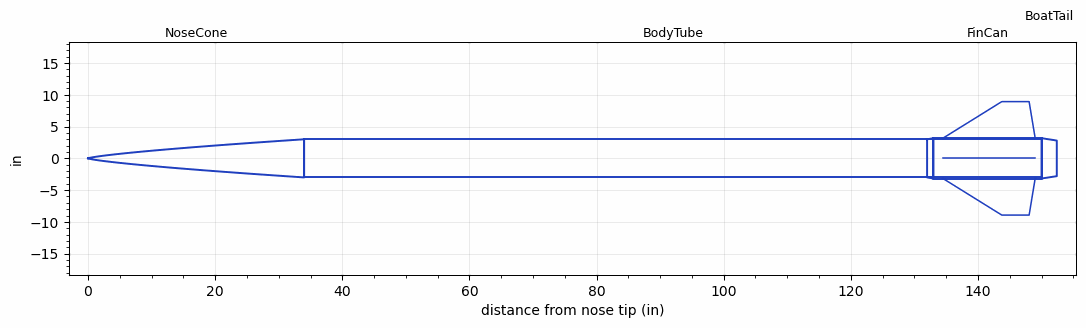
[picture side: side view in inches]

<RASAeroDocument>
 <FileVersion>2</FileVersion>
 <RocketDesign>
  <NoseCone>
   <Length>34</Length>
   <Diameter>6</Diameter>
   <Shape>Power Law</Shape>
   <BluntRadius>0.125</BluntRadius>
   <Location>0</Location>
   <PowerLaw>0.75</PowerLaw>
  </NoseCone>
  <BodyTube>
   <Length>116</Length>
   <Diameter>6</Diameter>
   <Location>34</Location>
  </BodyTube>
  <FinCan>
   <Length>17</Length>
   <Diameter>6.35</Diameter>
   <InsideDiameter>6</InsideDiameter>
   <Location>150</Location>
   <ShoulderLength>1</ShoulderLength>
   <Offset>-17</Offset>
   <Fin>
    <Count>4</Count>
    <Chord>14.5</Chord>
    <Span>5.75</Span>
    <SweepDistance>9.25</SweepDistance>
    <TipChord>4.3</TipChord>
    <Thickness>0.25</Thickness>
    <LERadius>0.08</LERadius>
    <Location>15.5</Location>
    <AirfoilSection>Hexagonal</AirfoilSection>
    <FX1>0.5</FX1>
    <FX3>0.25</FX3>
   </Fin>
  </FinCan>
  <BoatTail>
   <Length>2.4</Length>
   <Diameter>6.35</Diameter>
   <RearDiameter>5.6</RearDiameter>
   <Location>150</Location>
  </BoatTail>
  <Surface>Rough Camouflage Paint</Surface>
  <ModifiedBarrowman>True</ModifiedBarrowman>
  <Turbulence>True</Turbulence>
  <UseBooster1>False</UseBooster1>
  <UseBooster2>False</UseBooster2>
 </RocketDesign>
 <LaunchSite>
  <Altitude>3000</Altitude>
  <Pressure>0</Pressure>
  <RodAngle>2</RodAngle>
  <RodLength>18</RodLength>
  <Temperature>85</Temperature>
  <WindSpeed>8</WindSpeed>
 </LaunchSite>
 <Recovery>
  <Altitude1>1000</Altitude1>
  <Altitude2>10000</Altitude2>
  <DeviceType1>Parachute</DeviceType1>
  <DeviceType2>Parachute</DeviceType2>
  <Event1>True</Event1>
  <Event2>True</Event2>
  <Size1>60</Size1>
  <Size2>114</Size2>
  <EventType1>Apogee</EventType1>
  <EventType2>Altitude</EventType2>
  <CD1>0.48</CD1>
  <CD2>1.33</CD2>
 </Recovery>
 <SimulationList>
  <Simulation>
   <SustainerEngine>P9095  (MIT)</SustainerEngine>
   <SustainerLaunchWt>166.1</SustainerLaunchWt>
   <SustainerNozzleDiameter>4.7</SustainerNozzleDiameter>
   <SustainerCG>94.1</SustainerCG>
   <SustainerIgnitionDelay>0</SustainerIgnitionDelay>
   <Booster1SeparationDelay>0</Booster1SeparationDelay>
   <Booster1IgnitionDelay>0</Booster1IgnitionDelay>
   <IncludeBooster1>False</IncludeBooster1>
   <Booster2Delay>0</Booster2Delay>
   <IncludeBooster2>False</IncludeBooster2>
   <TimetoApogee>73.69733</TimetoApogee>
   <MaxAltitude>93650.04</MaxAltitude>
   <MaxVelocity>3374.477</MaxVelocity>
  </Simulation>
 </SimulationList>
</RASAeroDocument>
